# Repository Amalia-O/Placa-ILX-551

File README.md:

# Placa-ILX-551
Desarrollo de placa para el funcionamiento del sensor ILX-551

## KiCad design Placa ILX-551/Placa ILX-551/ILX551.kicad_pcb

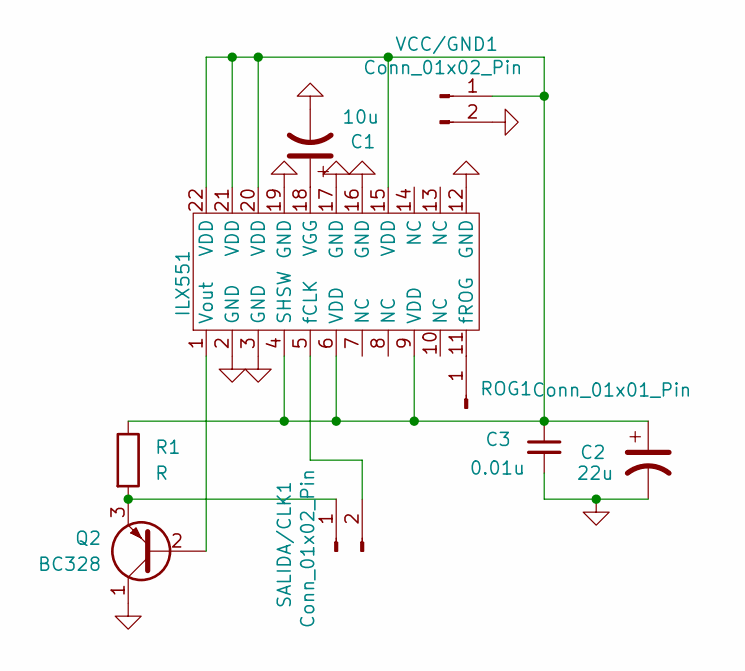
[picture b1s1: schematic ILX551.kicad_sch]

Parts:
C1: 10u; CP_Radial_D5.0mm_P2.50mm
C2: 22u; CP_Radial_D5.0mm_P2.50mm
C3: 0.01u; C_Disc_D8.0mm_W2.5mm_P5.00mm
ILX551: DIP-22_W10.16mm_Socket_LongPads
Q2: BC328; TO-92_Inline
R1: R; R_Axial_DIN0204_L3.6mm_D1.6mm_P2.54mm_Vertical
ROG1: Conn_01x01_Pin; PinHeader_1x01_P1.00mm_Vertical
SALIDA/CLK1: Conn_01x02_Pin; PinHeader_1x02_P2.54mm_Vertical
VCC/GND1: Conn_01x02_Pin; PinHeader_1x02_P2.54mm_Vertical

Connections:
GND: C1.2, C2.2, C3.2, ILX551.2 (GND), ILX551.3 (GND), ILX551.12 (GND), ILX551.16 (GND), ILX551.17 (GND), ILX551.19 (GND), Q2.1 (C), VCC/GND1.2
unnamed: C2.1, C3.1, ILX551.4 (SHSW), ILX551.6 (VDD), ILX551.9 (VDD), ILX551.15 (VDD), ILX551.20 (VDD), ILX551.21 (VDD), ILX551.22 (VDD), R1.1, VCC/GND1.1
unnamed: C1.1, ILX551.18 (VGG)
unnamed: ILX551.1 (Vout), Q2.2 (B)
unnamed: ILX551.5 (fCLK), SALIDA/CLK1.2
unnamed: ILX551.11 (fROG), ROG1.1
unnamed: Q2.3 (E), R1.2, SALIDA/CLK1.1

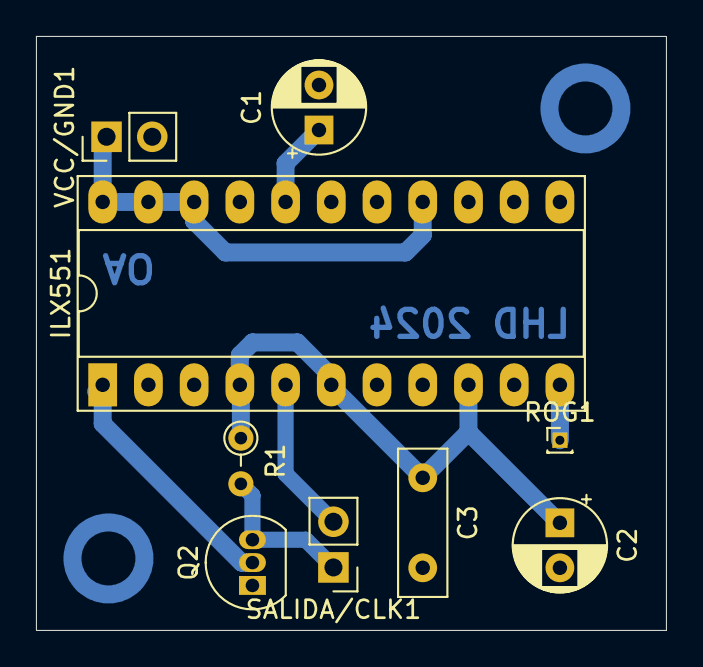
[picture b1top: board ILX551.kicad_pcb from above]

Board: 2 copper layers, 35.0 x 33.0 mm, 9 parts (0 on the bottom side), 7 nets.

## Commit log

2024-04-06 Add Kicad File
